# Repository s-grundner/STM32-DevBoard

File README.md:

# STM32 Devboard

With onboard Temp/Humidity Sensor and IMU

Primary goal is to use components I have stock

## Repository Structure

### [Documentation](/documentation/)

### [Manufacturing](/manufacturing/)

### [Simulations](/simulations/)

### [Source Code](/source/)

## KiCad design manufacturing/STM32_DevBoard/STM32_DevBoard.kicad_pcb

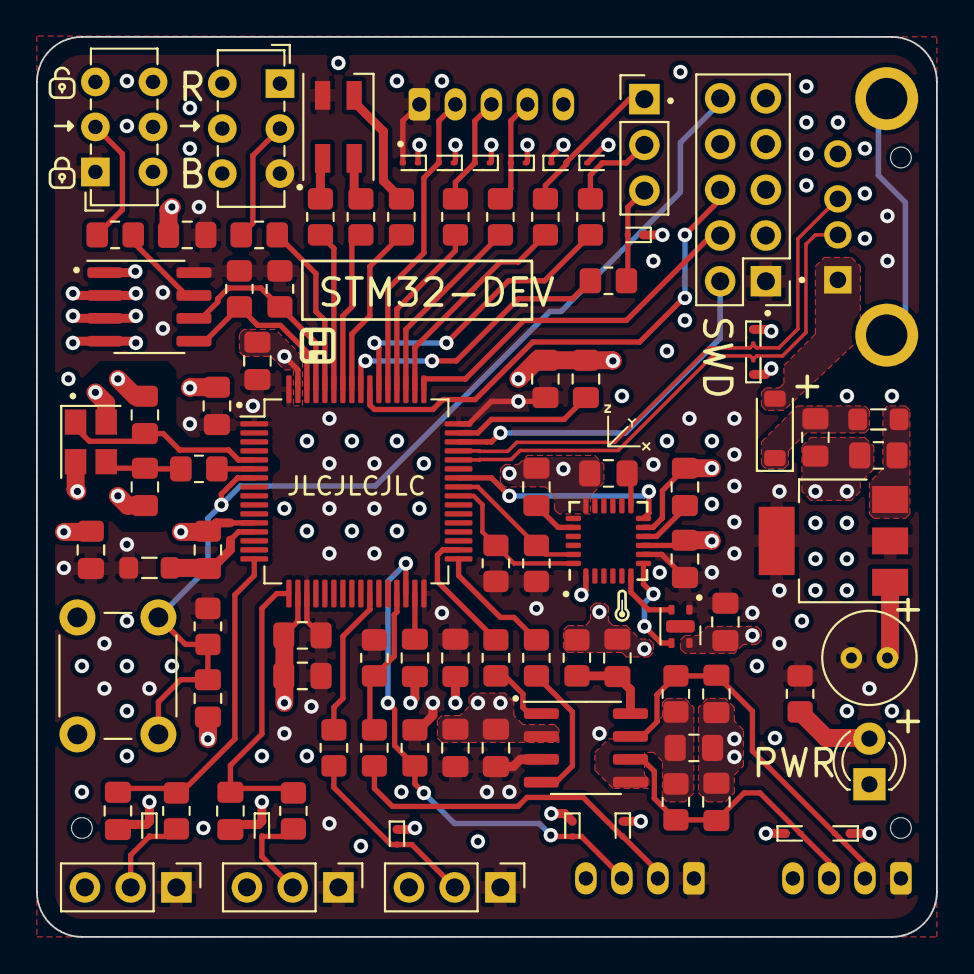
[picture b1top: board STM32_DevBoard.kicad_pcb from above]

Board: 4 copper layers, 50.0 x 50.0 mm, 101 parts (0 on the bottom side), 65 nets.

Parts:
C1, C2, C3, C4, C5, C7, C15, C17, C18, C20, C27, C28, C29, C30, C31: 100n; C_0805_2012Metric_Pad1.18x1.45mm_HandSolder
C6: 4u7; C_0805_2012Metric_Pad1.18x1.45mm_HandSolder
C8, C9, C10, C22, C26, C33: 2u2; C_0805_2012Metric_Pad1.18x1.45mm_HandSolder
C11, C12: 12p; C_0805_2012Metric_Pad1.18x1.45mm_HandSolder
C13: 820n; C_0805_2012Metric_Pad1.18x1.45mm_HandSolder
C14: 22u; C_Radial_D5.0mm_H7.0mm_P2.00mm
C16: 2n2; C_0805_2012Metric_Pad1.18x1.45mm_HandSolder
C19: 10n; C_0805_2012Metric_Pad1.18x1.45mm_HandSolder
C23, C25: 560n; C_0805_2012Metric_Pad1.18x1.45mm_HandSolder
D1: LED_RGBA; LED_SK6812MINI_PLCC4_3.5x3.5mm_P1.75mm
D2: GN; LED_D3.0mm
D3, D4, D5, D6, D7, D8, D9, D10, D11, D12, D13, D15, D17, D18, D20, D22: 3V3; D_SOD-923
D24: B5819W; D_SOD-123
FB1, FB2: 100R @ 100MHz; L_0805_2012Metric_Pad1.05x1.20mm_HandSolder
H4, H4#2, H4#3: JLC_Tooling
J1: CAN; Molex_Micro-Latch_53254-0470_1x04_P2.00mm_Horizontal
J3, J12: AGPIO; PinHeader_1x03_P2.54mm_Vertical
J5: USB_A; USB_A_CONNFLY_DS1095-WNR0
J6: SWD; PinHeader_2x05_P2.54mm_Vertical
J8: SPI/UART; Molex_Micro-Latch_53254-0570_1x05_P2.00mm_Horizontal
J9: SPI_NSS/GPIO; PinHeader_1x03_P2.54mm_Vertical
J10: I2C; Molex_Micro-Latch_53254-0470_1x04_P2.00mm_Horizontal
J11: PWM0; PinHeader_1x03_P2.54mm_Vertical
R1: 0R; R_0805_2012Metric_Pad1.20x1.40mm_HandSolder
R2, R3, R8: 10k; R_0805_2012Metric_Pad1.20x1.40mm_HandSolder
R4, R5, R6, R11, R23, R24, R25, R26, R27, R28: 1k5; R_0805_2012Metric_Pad1.20x1.40mm_HandSolder
R7, R17, R18, R19, R20, R21, R22: 10R; R_0805_2012Metric_Pad1.20x1.40mm_HandSolder
R9, R14: 47R; R_0805_2012Metric_Pad1.20x1.40mm_HandSolder
R10, R12: 150R; R_0805_2012Metric_Pad1.20x1.40mm_HandSolder
R13, R15: 56R; R_0805_2012Metric_Pad1.20x1.40mm_HandSolder
R16: 5k6; R_0805_2012Metric_Pad1.20x1.40mm_HandSolder
SW1: SW_SPDT; SW_E-Switch_EG1271_SPDT
SW2: SW_Omron_B3FS; SW_PUSH_6mm
SW3: EEPROM_WP; SW_E-Switch_EG1271_SPDT
U1: MPU-6050; InvenSense_QFN-24_4x4mm_P0.5mm
U2: SHTC3; Sensirion_DFN-4-1EP_2x2mm_P1mm_EP0.7x1.6mm
U3: STM32F405RGT6; LQFP-64_10x10mm_P0.5mm
U4: AT24C256; SOIC-8_3.9x4.9mm_P1.27mm
U6: SN65HVD230; SOIC-8_3.9x4.9mm_P1.27mm
U8: AMS1117-3.3; SOT-223-3_TabPin2
Y1: 25MHz 12pF; Crystal_SMD_3225-4Pin_3.2x2.5mm

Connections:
+3V3: C1.1, C2.1, C3.1, C4.1, C5.1, C6.1, C8.1, C14.1, C17.1, C18.1, C19.1, C20.1, C26.1, C27.1, D1.4 (A), D3.2 (A2), FB1.2, J1.1, J3.1, J6.1, J8.1, J10.1, J11.1, J12.1, R3.1, R11.2, R23.1, R24.1, R25.1, R26.1, R27.1, R28.1, SW1.3 (C), SW3.1 (A), U1.8 (VLOGIC), U1.13 (VDD), U2.1 (VDD), U3.1 (VBAT), U3.19 (VDD), U3.32 (VDD), U3.48 (VDD), U3.64 (VDD), U4.8 (VCC), U6.3 (VCC), U8.2 (VO)
+3V3A: C7.1, FB1.1, U3.13 (VDDA)
+5V: D24.2 (A), J5.1 (VBUS)
/Connectors/A_GPIO_2: C25.1, R12.1, U3.16 (PA2)
/Connectors/A_GPIO_3: C23.1, R10.1, U3.17 (PA3)
/Connectors/CAN+: C28.1, D20.2 (A2), J1.2, R13.2, U6.7 (CANH)
/Connectors/CAN-: C30.2, D15.2 (A2), J1.3, R15.1, U6.6 (CANL)
/Connectors/CAN_RS: C31.1, R16.2, U6.8 (Rs)
/Connectors/CAN_RX: R14.1, U3.33 (PB12)
/Connectors/CAN_TX: R9.1, U3.34 (PB13)
/Connectors/I2C_SCL: R22.1, R27.2, U3.29 (PB10)
/Connectors/I2C_SDA: D17.2 (A2), J10.3, R28.2, U3.30 (PB11)
/Connectors/PWM0: R17.1, U3.26 (PB0)
/Connectors/SPI_MISO_RX: R21.1, U3.52 (PC11)
/Connectors/SPI_MOSI: D4.2 (A2), J8.2, U3.53 (PC12)
/Connectors/SPI_NSS0: R18.1, U3.50 (PA15)
/Connectors/SPI_NSS1: R19.1, U3.54 (PD2)
/Connectors/SPI_NSS2: R20.1, U3.56 (PB4)
/Connectors/SPI_SCK_TX: R7.1, U3.51 (PC10)
/Connectors/USB_D+: D5.2 (A2), J5.3 (D+), U3.45 (PA12)
/Connectors/USB_D-: D6.2 (A2), J5.2 (D-), U3.44 (PA11)
/Connectors/VREF: C29.1, R13.1, R15.2, U6.5 (Vref)
/MCU/EEPROM_SCL: R24.2, U3.61 (PB8), U4.6 (SCL)
/MCU/EEPROM_SDA: R23.2, U3.62 (PB9), U4.5 (SDA)
/MCU/EEPROM_WP: R8.2, U4.7 (WP)
/MCU/EEPROM_WP_SW: R8.1, SW3.2 (B)
/MCU/IMU_INT: U1.12 (INT), U3.42 (PA9)
/MCU/NPWM_B: R6.1, U3.57 (PB5)
/MCU/NPWM_G: R5.1, U3.58 (PB6)
/MCU/NPWM_R: R4.1, U3.59 (PB7)
/MCU/NRST: C13.1, J6.10, R3.2, SW2.2, U3.7 (NRST)
/MCU/SENSE_SCL: R25.2, U1.23 (SCL), U3.41 (PA8)
/MCU/SENSE_SDA: R26.2, U1.24 (SDA), U3.40 (PC9)
/MCU/SWCLK: J6.4, U3.49 (PA14)
/MCU/SWDIO: J6.2, U3.46 (PA13)
/MCU/SWO: J6.6, U3.55 (PB3)
/MCU/Strapping/BOOT0: R2.2, U3.60 (BOOT0)
/MCU/Strapping/HSE_IN: C11.1, U3.5 (PH0), Y1.1
/MCU/Strapping/HSE_OUT: R1.2, U3.6 (PH1)
/MCU/Strapping/XTAL_IN: C12.1, R1.1, Y1.3
/PMU/LDO_IN: C33.1, FB2.1, U8.3 (VI)
/PMU/POST_POL: C22.1, D24.1 (K), FB2.2
/Sensors/AUX_SCL: U1.6 (AUX_DA), U2.2 (SCL)
/Sensors/AUX_SDA: U1.7 (AUX_CL), U2.3 (SDA)
GND: C1.2, C2.2, C3.2, C4.2, C5.2, C6.2, C7.2, C8.2, C9.2, C10.2, C11.2, C12.2, C13.2, C14.2, C15.2, C16.2, C17.2, C18.2, C19.2, C20.2, C22.2, C23.2, C25.2, C26.2, C27.2, C28.2, C29.2, C30.1, C31.2, C33.2, D2.1 (K), D3.1 (A1), D4.1 (A1), D5.1 (A1), D6.1 (A1), D7.1 (A1), D8.1 (A1), D9.1 (A1), D10.1 (A1), D11.1 (A1), D12.1 (A1), D13.1 (A1), D15.1 (A1), D17.1 (A1), D18.1 (A1), D20.1 (A1), D22.1 (A1), J1.4, J3.3, J5.4 (GND), J6.3, J6.5, J6.9, J8.5, J10.4, J11.3, J12.3, R16.1, SW1.1 (A), SW2.1, SW3.3 (C), U1.1 (CLKIN), U1.9 (AD0), U1.11 (FSYNC), U1.18 (GND), U2.4 (VSS), U3.12 (VSSA), U3.18 (VSS), U3.63 (VSS), U4.1 (A0), U4.2 (A1), U4.3 (A2), U4.4 (GND), U6.2 (GND), U8.1 (GND), Y1.2, Y1.4
unnamed: D1.3 (BK), R6.2
unnamed: D1.2 (GK), R5.2
unnamed: D1.1 (RK), R4.2
unnamed: D2.2 (A), R11.1
unnamed: D7.2 (A2), J3.2, R10.2
unnamed: D8.2 (A2), J8.3, R21.2
unnamed: D9.2 (A2), J8.4, R7.2
unnamed: D10.2 (A2), J9.3, R20.2
unnamed: D11.2 (A2), J9.2, R19.2
unnamed: D12.2 (A2), J9.1, R18.2
unnamed: D13.2 (A2), J11.2, R17.2
unnamed: D18.2 (A2), J10.2, R22.2
unnamed: D22.2 (A2), J12.2, R12.2
unnamed: R2.1, SW1.2 (B)
unnamed: C16.1, U1.20 (CPOUT)
unnamed: C15.1, U1.10 (REGOUT)
unnamed: C10.1, U3.31 (VCAP_1)
unnamed: C9.1, U3.47 (VCAP_2)
unnamed: R9.2, U6.1 (D)
unnamed: R14.2, U6.4 (R)

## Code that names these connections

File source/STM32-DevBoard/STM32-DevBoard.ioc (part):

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Mcu.Name=STM32F405RGTx
Mcu.Package=LQFP64
Mcu.UserName=STM32F405RGTx
PA0-WKUP.Signal=ADCx_IN0
PA1.Signal=ADCx_IN1
PA11.Mode=Device_Only
PA11.Signal=USB_OTG_FS_DM
PA12.Mode=Device_Only
PA12.Signal=USB_OTG_FS_DP
PA13.Mode=Trace_Asynchronous_SW
PA13.Signal=SYS_JTMS-SWDIO
PA14.Mode=Trace_Asynchronous_SW
PA14.Signal=SYS_JTCK-SWCLK
PA15.GPIOParameters=GPIO_Label
PA15.GPIO_Label=SPI3_NSS0
PA15.Mode=NSS_Signal_Hard_Output
PA15.Signal=SPI3_NSS
PA2.Signal=ADCx_IN2
PA3.Signal=ADCx_IN3
PA4.Signal=ADCx_IN4
PA5.Signal=ADCx_IN5
PA6.Signal=ADCx_IN6
PA7.Signal=ADCx_IN7
PA8.Mode=SMBus-Alert-mode
PA8.Signal=I2C3_SCL
PA9.Mode=SMBus-Alert-mode
PA9.Signal=I2C3_SMBA
PB0.Signal=S_TIM3_CH3
PB1.Signal=S_TIM3_CH4
PB10.Mode=I2C
PB10.Signal=I2C2_SCL
PB11.Mode=I2C
PB11.Signal=I2C2_SDA
PB12.Mode=CAN_Activate
PB12.Signal=CAN2_RX
PB13.Mode=CAN_Activate
PB13.Signal=CAN2_TX
PB3.Mode=Trace_Asynchronous_SW
PB3.Signal=SYS_JTDO-SWO
PB4.GPIOParameters=GPIO_Label
PB4.GPIO_Label=SPI3_NSS2
PB4.Signal=GPIO_Output
PB5.Signal=S_TIM3_CH2
PB6.Signal=S_TIM4_CH1
PB7.Signal=S_TIM4_CH2
PB8.Mode=I2C
PB8.Signal=I2C1_SCL
PB9.Mode=I2C
PB9.Signal=I2C1_SDA
PC10.Mode=Full_Duplex_Master
PC10.Signal=SPI3_SCK
PC11.Mode=Full_Duplex_Master
PC11.Signal=SPI3_MISO
PC12.Mode=Full_Duplex_Master
PC12.Signal=SPI3_MOSI
PC9.Mode=SMBus-Alert-mode
PC9.Signal=I2C3_SDA
PD2.GPIOParameters=GPIO_Label
PD2.GPIO_Label=SPI3_NSS1
PD2.Signal=GPIO_Output
PH0-OSC_IN.Mode=HSE-External-Oscillator
PH0-OSC_IN.Signal=RCC_OSC_IN
PH1-OSC_OUT.Mode=HSE-External-Oscillator
PH1-OSC_OUT.Signal=RCC_OSC_OUT
RCC.HSE_VALUE=25000000
RCC.SYSCLKFreq_VALUE=168000000
RCC.SYSCLKSource=RCC_SYSCLKSOURCE_PLLCLK
board=custom

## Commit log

2023-08-20 added BSB
2023-08-20 create Kicad project
2023-08-20 upd Schematic
2023-08-20 Revision 1 Prototype
2023-08-20 pinout and Low Level Drivers
2023-08-23 update Board Revision 0
